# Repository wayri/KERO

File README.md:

# KERO — RC-programmed hello world pulse encoder

> **AI hardware-design experiment:** KERO evaluates AI-generated electronic schematics and PCB layouts. This is an experimental design for engineering review; hardware has not been built or bench tested.

One **CR2032** powers a repeating `hello world` pulse encoder made from **three TLV9044IPWR quad op-amps**, resistors and capacitors, with red/green LED indication. R/C values program the pulse sequence. The complete encoder, local libraries, 3D models, BoM and saved analysis are included on `main` following [PR #16](https://github.com/wayri/KERO/pull/16).

## Open the encoder

Open [encoder/Encoder.kicad_pro](encoder/Encoder.kicad_pro) in **KiCad 10** (saved verification: 10.0.6). The two-layer board is **40 × 40 mm**, with the circuit on the front and coin-cell holder on the back.

- [Encoder guide](encoder/README.md) · [BoM](encoder/bom.csv) · [Pin/net design intent](encoder/design-intent.json)
- [Schematic and shared variables](encoder/SCHEMATIC.md) · [Timing architecture and R/C values](encoded-model/architecture.md)
- [Front copper](encoder/previews/board-front.svg) · [Back copper](encoder/previews/board-back.svg)
- [Curved-routing evidence](encoder/evidence/curved-routing.json): native tangent arcs are the default; 678 staircase segments removed and 685 arc bends added.
- [Power, PI and thermal analysis files](encoder/analysis/README.md) — saved for the preceding straight-track board; copper overlays have not been rerun after smoothing.

All 79 fitted parts resolve local package models. The illustrated coin cell is a nominal envelope, not a manufacturer-qualified fit model. The CR2032 cell is a separate assembly item from BT1's holder; exact passive and LED order codes remain unverified in the BoM.

## Hierarchical schematic

The six wired sheets separate power, three timing banks and the output decoder. Shared project variables assign component values and common part details.

[Power](encoder/previews/Encoder-power.svg) · [Timing bank 1](encoder/previews/Encoder-bank1.svg) · [Timing bank 2](encoder/previews/Encoder-bank2.svg) · [Timing bank 3](encoder/previews/Encoder-bank3.svg) · [Output decoder](encoder/previews/Encoder-decoder.svg)

## Pulse sequence

Eleven inverting Schmitt op-amp stages form a timing ring. The twelfth channel combines the ring outputs through a resistive-majority network. Each complete frame emits the eleven symbols in `hello world`; the output and LEDs indicate the encoded pulses. The transmitter uses no MCU or separate logic IC.

| Pulse parameter | Programmed value |
|---|---|
| Codebook | space=0, d=1, e=2, h=3, l=4, o=5, r=6, w=7 |
| High pulse width | 50 ms × 1.3^code |
| Ordinary low gap | 100 ms |
| Final low gap / frame delimiter | 1 s |
| Nominal repeating frame | 3.664 s |
| Symbol-index payload | 33 bits, excluding codebook/framing overhead |

A receiver must recognize the long gap and decode the high pulse widths using this codebook. This is an electrical pulse output with LED indication, not ASCII, UART or radio. Changing R/C values changes the timing sequence. Startup, residual capacitor charge and supply ramps affect initial frames; see the [model boundaries and executed simulation](encoded-model/architecture.md) and [SPICE evidence](encoded-model/spice/README.md).

## Saved verification

| Check | Saved result |
|---|---|
| Schematic ERC | 0 violations across six sheets |
| PCB DRC / schematic parity | 0 reported findings / 0 mismatches |
| Connectivity | 0 open connections; all 40 nets connected |
| Circuit identity | 79 parts and 194 pad assignments checked |
| Routing repair | Dangling terminal stubs removed; track/via changes only |

[Board validation](encoder/evidence/board-validation.json) · [Native DRC](encoder/evidence/board-drc.json) · [Circuit equivalence](encoder/evidence/circuit-equivalence.json) · [Routing comparison](encoder/evidence/routing-change.json)

Five pre-existing default ignored DRC checks remain disclosed in the reports; no rule severity was relaxed. These are saved native checks and simulation evidence, not fabrication or bench qualification. Component sourcing, tolerances, leakage, startup and useful battery life still require hardware assessment.

## Coin-cell draw, losses and thermal analysis

These saved studies describe the preceding straight-track board revision. The circuit is unchanged, but PI and thermal copper overlays have not been rerun after smoothing.

| Saved model result | Value |
|---|---|
| Mean / RMS cell current at 3 V | 279.081 / 279.149 µA |
| Sampled settled peak current | 290.788 µA |
| Startup peak with 1 ms supply ramp | 1.174 mA |
| Component heat | 837.244 µW |
| Mean-load VBAT copper drop | 45.762 µV |
| Maximum board temperature at 25 °C ambient | 25.166 °C |

The [analysis index](encoder/analysis/README.md) includes native WayriCAD PI and QuickTherm results, extension-compatible companions, full compressed waveforms, per-component losses, cell-resistance scenarios, configurations, logs and source hashes.

These are model estimates. Local PI current-density peaks remain unconverged, and the mean-GND mesh has an unresolved region at C4. Ground fields use a shifted/reversed mathematical reference. QuickTherm estimates board temperature under declared material/convection assumptions; junction temperature, cell internal heat and electrothermal feedback are outside that solve. Vendor-model current reconstruction and other limitations remain documented. No measured battery-life claim is made.

## Review and comparison demos

[PR #16 — encoder, routing closure and analysis](https://github.com/wayri/KERO/pull/16) records the current project's development. [DEMO.md](DEMO.md) covers the comparison walkthrough, with earlier blinker changes in [PR #5](https://github.com/wayri/KERO/pull/5) (timing), [#6](https://github.com/wayri/KERO/pull/6) (layout), [#7](https://github.com/wayri/KERO/pull/7) (documentation), [#8](https://github.com/wayri/KERO/pull/8) (BoM), and [#9](https://github.com/wayri/KERO/pull/9) (mixed ECO).

## Legacy LED blinker

The root [KERO.kicad_pro](KERO.kicad_pro) is the earlier LMV358A alternating-LED oscillator, retained for historical comparisons. Its [schematic](previews/KERO.svg), [BoM](bom.csv) and [analysis](analysis/README.md) describe that older board. Use `encoder/Encoder.kicad_pro` and `encoder/analysis/` for the current pulse encoder.

## Models and attribution

Local KiCad library assets retain their [library license](LICENSE.KiCad.md), **CC-BY-SA-4.0 with the KiCad libraries exception**. See [asset provenance](ASSETS.md) and the [encoder model validation](encoder/evidence/board-validation.json). No IRCA files or proprietary thermal-camera circuitry are included.

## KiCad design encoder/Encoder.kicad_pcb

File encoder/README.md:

# KERO hello world encoder — draft hardware

> **AI hardware-design experiment:** KERO is an experiment to evaluate how well AI can generate and refine electronic schematics and PCB layouts. The designs are experimental candidates for engineering review and validation.

Saved [encoder cell-draw, PI and QuickTherm studies](analysis/README.md) describe the preceding straight-track board revision; the copper fields have not been rerun for the curved routing.

Open [Encoder.kicad_pro](Encoder.kicad_pro) in KiCad 10. The [six-sheet schematic](Encoder.kicad_sch) implements an RC-programmed `hello world` PWM sequence using three TLV9044IPWR quad op amps, one CR2032 cell, and alternating red/green indication. See [circuit operation and timing](../encoded-model/architecture.md), [executed SPICE evidence](../encoded-model/spice/README.md), and [schematic/variables guide](SCHEMATIC.md).

| Saved design check | Result |
|---|---|
| Native schematic ERC | 0 violations |
| Components / pad assignments | 79 / 194; exact intent and schematic parity |
| Board size | 40 × 40 mm; 44.9% less area than the original blinker |
| Placement | Front circuit, bottom coin-cell holder |
| Native routing status | **Complete: 0 open connections; all 40 nets connected** |
| Native DRC / schematic parity | 0 reported findings / 0 mismatches |
| Models | All 79 fitted parts resolve local standard package models; nominal cell is illustrative |

The default routing style is **native tangent circular arcs at bends**, with straight runs and fixed pad/via/branch landings. The [curved-routing receipt](evidence/curved-routing.json) records 678 redundant staircase segments removed and 685 native arc bends. One clearance-constrained GND path keeps its original corridor. [Routing guidance](AGENTS.md) defines the convention for future edits.

The routing repair removed dangling terminal stubs and negotiated alternate copper paths without moving components or changing the circuit or rules. [Revision comparison](evidence/routing-change.json) records only track/via changes; [circuit equivalence](evidence/circuit-equivalence.json) independently checks all 79 parts and 194 assignments against the simulated design. The native ERC, DRC, parity and connectivity checks pass. Five pre-existing default ignored DRC checks remain listed in the report; no severities or exclusions were changed.

This is a review candidate, not a fabrication release. [Board validation](evidence/board-validation.json) lists the connected pad partitions and check settings; [native DRC](evidence/board-drc.json) retains all reported findings. Source hashes were checked against the files being published. KiCad local preference files and tool scratch are excluded from Git; the original native command receipt retains the local preference-file hash as incidental execution context.

The [BoM](bom.csv) contains values, packages, manufacturer/MPN fields and ratings. Exact passive and LED order codes remain unverified and are marked `Select to specification`; no procurement closure is claimed. The CR2032 cell is a separate assembly consumable from BT1, the Keystone holder. Local KiCad libraries and package models follow the repository [asset provenance](../ASSETS.md) and [KiCad library license](../LICENSE.KiCad.md).

The root `KERO.kicad_*` files remain the earlier validated blinker. Saved PI/QuickTherm files under `../analysis/` describe that root board only; no new encoder PI or thermal solve is represented by those files.

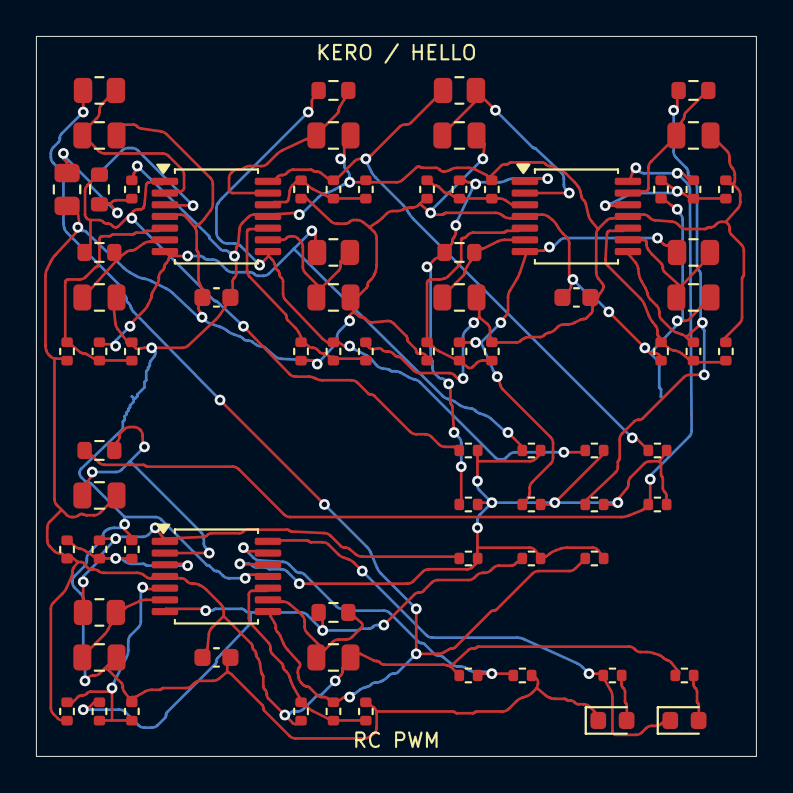
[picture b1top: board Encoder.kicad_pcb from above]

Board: 2 copper layers, 40.0 x 40.0 mm, 79 parts (1 on the bottom side), 40 nets.

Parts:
BT1: CR2032; BatteryHolder_Keystone_1058_1x2032
C1, C2, C3, C4, C5, C6, C7, C8, C9, C10, C11: 47n; C_0805_2012Metric
C12, C13, C14: 100n; C_0603_1608Metric
D1: RED; LED_0603_1608Metric
D2: GREEN; LED_0603_1608Metric
R1: 6.98M; R_0805_2012Metric
R2: 2.13M; R_0805_2012Metric
R3: 1.05M; R_0603_1608Metric
R4: 117k; R_0402_1005Metric
R5: 1.65M; R_0603_1608Metric
R6: 365k; R_0402_1005Metric
R7, R26: 208k; R_0402_1005Metric
R8: 412k; R_0402_1005Metric
R9: 3.52M; R_0805_2012Metric
R10: 182k; R_0402_1005Metric
R11: 332k; R_0402_1005Metric
R12: 665k; R_0402_1005Metric
R13: 1.47M; R_0603_1608Metric
R14: 427k; R_0402_1005Metric
R15: 213k; R_0402_1005Metric
R16: 340k; R_0402_1005Metric
R17, R37: 2.43M; R_0805_2012Metric
R18, R38: 240k; R_0402_1005Metric
R19, R39: 258k; R_0402_1005Metric
R20, R40: 511k; R_0402_1005Metric
R21, R29, R33: 2M; R_0603_1608Metric
R22, R27, R30, R34: 291k; R_0402_1005Metric
R23, R31, R35: 229k; R_0402_1005Metric
R24, R32, R36: 459k; R_0402_1005Metric
R25: 2.91M; R_0805_2012Metric
R28: 583k; R_0402_1005Metric
R41: 1.37M; R_0603_1608Metric
R42: 470k; R_0402_1005Metric
R43: 237k; R_0402_1005Metric
R44: 274k; R_0402_1005Metric
R45, R46, R47, R48, R49, R50, R51, R52, R53, R54, R55: 1M; R_0402_1005Metric
R56, R57: 100k; R_0402_1005Metric
R58, R59: 15k; R_0402_1005Metric
U1, U2, U3: TLV9044IPWR; TSSOP-14_4.4x5mm_P0.65mm

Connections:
/GND: BT1.2, C2.2, C4.2, C6.2, C8.2, C10.2, C12.2, C13.2, C14.2, D1.1, R4.2, R8.2, R12.2, R16.2, R20.2, R24.2, R28.2, R32.2, R36.2, R40.2, R44.2, R57.2, U1.11, U2.11, U3.11
/ST01_OUT: R3.2, R5.1, R45.1, U1.1
/ST02_OUT: R7.2, R9.1, R46.1, U1.7
/ST03_OUT: R11.2, R13.1, R47.1, U1.8
/ST04_OUT: R15.2, R17.1, R48.1, U1.14
/ST05_OUT: R19.2, R21.1, R49.1, U2.1
/ST06_OUT: R23.2, R25.1, R50.1, U2.7
/ST07_OUT: R27.2, R29.1, R51.1, U2.8
/ST08_OUT: R31.2, R33.1, R52.1, U2.14
/ST09_OUT: R35.2, R37.1, R53.1, U3.1
/ST10_OUT: R39.2, R41.1, R54.1, U3.7
/ST11_OUT: R1.1, R43.2, R55.1, U3.8
/VBAT: BT1.1, C1.2, C3.2, C5.2, C7.2, C9.2, C11.2, C12.1, C13.1, C14.1, R2.1, R6.1, R10.1, R14.1, R18.1, R22.1, R26.1, R30.1, R34.1, R38.1, R42.1, R56.1, R59.1, U1.4, U2.4, U3.4
/bank1/ST01_TH: R2.2, R3.1, R4.1, U1.3
/bank1/ST01_TIMING: C1.1, R1.2, U1.2
/bank1/ST02_TH: R6.2, R7.1, R8.1, U1.5
/bank1/ST02_TIMING: C2.1, R5.2, U1.6
/bank1/ST03_TH: R10.2, R11.1, R12.1, U1.10
/bank1/ST03_TIMING: C3.1, R9.2, U1.9
/bank1/ST04_TH: R14.2, R15.1, R16.1, U1.12
/bank1/ST04_TIMING: C4.1, R13.2, U1.13
/bank2/ST05_TH: R18.2, R19.1, R20.1, U2.3
/bank2/ST05_TIMING: C5.1, R17.2, U2.2
/bank2/ST06_TH: R22.2, R23.1, R24.1, U2.5
/bank2/ST06_TIMING: C6.1, R21.2, U2.6
/bank2/ST07_TH: R26.2, R27.1, R28.1, U2.10
/bank2/ST07_TIMING: C7.1, R25.2, U2.9
/bank2/ST08_TH: R30.2, R31.1, R32.1, U2.12
/bank2/ST08_TIMING: C8.1, R29.2, U2.13
/bank3/ST09_TH: R34.2, R35.1, R36.1, U3.3
/bank3/ST09_TIMING: C9.1, R33.2, U3.2
/bank3/ST10_TH: R38.2, R39.1, R40.1, U3.5
/bank3/ST10_TIMING: C10.1, R37.2, U3.6
/bank3/ST11_TH: R42.2, R43.1, R44.1, U3.10
/bank3/ST11_TIMING: C11.1, R41.2, U3.9
/decoder/GREEN_A: D2.2, R59.2
/decoder/MAJORITY_SUM: R45.2, R46.2, R47.2, R48.2, R49.2, R50.2, R51.2, R52.2, R53.2, R54.2, R55.2, U3.12
/decoder/MIDREF: R56.2, R57.1, U3.13
/decoder/RED_A: D1.2, R58.2
ENCODED_OUT: D2.1, R58.1, U3.14

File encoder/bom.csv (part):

Reference,Quantity,Value,Footprint,Manufacturer,MPN,Rating,Datasheet
U1,1,TLV9044IPWR,Encoder:TSSOP-14_4.4x5mm_P0.65mm,Texas Instruments,TLV9044IPWR,1.2–5.5 V RRIO quad op amp,https://www.ti.com/lit/ds/symlink/tlv9044.pdf
U2,1,TLV9044IPWR,Encoder:TSSOP-14_4.4x5mm_P0.65mm,Texas Instruments,TLV9044IPWR,1.2–5.5 V RRIO quad op amp,https://www.ti.com/lit/ds/symlink/tlv9044.pdf
U3,1,TLV9044IPWR,Encoder:TSSOP-14_4.4x5mm_P0.65mm,Texas Instruments,TLV9044IPWR,1.2–5.5 V RRIO quad op amp,https://www.ti.com/lit/ds/symlink/tlv9044.pdf
R1,1,6.98M,Encoder:R_0805_2012Metric,Select to specification,Select to specification,"0.1%, 0805; exact MPN unverified",
R2,1,2.13M,Encoder:R_0805_2012Metric,Select to specification,Select to specification,"0.1%, 0805; exact MPN unverified",
R3,1,1.05M,Encoder:R_0603_1608Metric,Select to specification,Select to specification,"0.1%, 0603; exact MPN unverified",
R4,1,117k,Encoder:R_0402_1005Metric,Select to specification,Select to specification,"0.1%, 0402; exact MPN unverified",
C1,1,47n,Encoder:C_0805_2012Metric,Select to specification,Select to specification,"47 nF, C0G, 1%, 0805; exact MPN unverified",
R5,1,1.65M,Encoder:R_0603_1608Metric,Select to specification,Select to specification,"0.1%, 0603; exact MPN unverified",
R6,1,365k,Encoder:R_0402_1005Metric,Select to specification,Select to specification,"0.1%, 0402; exact MPN unverified",
R7,1,208k,Encoder:R_0402_1005Metric,Select to specification,Select to specification,"0.1%, 0402; exact MPN unverified",
R8,1,412k,Encoder:R_0402_1005Metric,Select to specification,Select to specification,"0.1%, 0402; exact MPN unverified",
C2,1,47n,Encoder:C_0805_2012Metric,Select to specification,Select to specification,"47 nF, C0G, 1%, 0805; exact MPN unverified",
R9,1,3.52M,Encoder:R_0805_2012Metric,Select to specification,Select to specification,"0.1%, 0805; exact MPN unverified",
R10,1,182k,Encoder:R_0402_1005Metric,Select to specification,Select to specification,"0.1%, 0402; exact MPN unverified",
R11,1,332k,Encoder:R_0402_1005Metric,Select to specification,Select to specification,"0.1%, 0402; exact MPN unverified",
R12,1,665k,Encoder:R_0402_1005Metric,Select to specification,Select to specification,"0.1%, 0402; exact MPN unverified",
C3,1,47n,Encoder:C_0805_2012Metric,Select to specification,Select to specification,"47 nF, C0G, 1%, 0805; exact MPN unverified",
R13,1,1.47M,Encoder:R_0603_1608Metric,Select to specification,Select to specification,"0.1%, 0603; exact MPN unverified",
R14,1,427k,Encoder:R_0402_1005Metric,Select to specification,Select to specification,"0.1%, 0402; exact MPN unverified",
R15,1,213k,Encoder:R_0402_1005Metric,Select to specification,Select to specification,"0.1%, 0402; exact MPN unverified",
R16,1,340k,Encoder:R_0402_1005Metric,Select to specification,Select to specification,"0.1%, 0402; exact MPN unverified",
C4,1,47n,Encoder:C_0805_2012Metric,Select to specification,Select to specification,"47 nF, C0G, 1%, 0805; exact MPN unverified",
R17,1,2.43M,Encoder:R_0805_2012Metric,Select to specification,Select to specification,"0.1%, 0805; exact MPN unverified",
R18,1,240k,Encoder:R_0402_1005Metric,Select to specification,Select to specification,"0.1%, 0402; exact MPN unverified",
R19,1,258k,Encoder:R_0402_1005Metric,Select to specification,Select to specification,"0.1%, 0402; exact MPN unverified",
R20,1,511k,Encoder:R_0402_1005Metric,Select to specification,Select to specification,"0.1%, 0402; exact MPN unverified",
C5,1,47n,Encoder:C_0805_2012Metric,Select to specification,Select to specification,"47 nF, C0G, 1%, 0805; exact MPN unverified",
R21,1,2M,Encoder:R_0603_1608Metric,Select to specification,Select to specification,"0.1%, 0603; exact MPN unverified",
R22,1,291k,Encoder:R_0402_1005Metric,Select to specification,Select to specification,"0.1%, 0402; exact MPN unverified",
R23,1,229k,Encoder:R_0402_1005Metric,Select to specification,Select to specification,"0.1%, 0402; exact MPN unverified",
R24,1,459k,Encoder:R_0402_1005Metric,Select to specification,Select to specification,"0.1%, 0402; exact MPN unverified",
C6,1,47n,Encoder:C_0805_2012Metric,Select to specification,Select to specification,"47 nF, C0G, 1%, 0805; exact MPN unverified",
R25,1,2.91M,Encoder:R_0805_2012Metric,Select to specification,Select to specification,"0.1%, 0805; exact MPN unverified",
R26,1,208k,Encoder:R_0402_1005Metric,Select to specification,Select to specification,"0.1%, 0402; exact MPN unverified",
R27,1,291k,Encoder:R_0402_1005Metric,Select to specification,Select to specification,"0.1%, 0402; exact MPN unverified",
R28,1,583k,Encoder:R_0402_1005Metric,Select to specification,Select to specification,"0.1%, 0402; exact MPN unverified",
C7,1,47n,Encoder:C_0805_2012Metric,Select to specification,Select to specification,"47 nF, C0G, 1%, 0805; exact MPN unverified",
R29,1,2M,Encoder:R_0603_1608Metric,Select to specification,Select to specification,"0.1%, 0603; exact MPN unverified",
R30,1,291k,Encoder:R_0402_1005Metric,Select to specification,Select to specification,"0.1%, 0402; exact MPN unverified",
R31,1,229k,Encoder:R_0402_1005Metric,Select to specification,Select to specification,"0.1%, 0402; exact MPN unverified",
R32,1,459k,Encoder:R_0402_1005Metric,Select to specification,Select to specification,"0.1%, 0402; exact MPN unverified",
C8,1,47n,Encoder:C_0805_2012Metric,Select to specification,Select to specification,"47 nF, C0G, 1%, 0805; exact MPN unverified",
R33,1,2M,Encoder:R_0603_1608Metric,Select to specification,Select to specification,"0.1%, 0603; exact MPN unverified",
R34,1,291k,Encoder:R_0402_1005Metric,Select to specification,Select to specification,"0.1%, 0402; exact MPN unverified",
R35,1,229k,Encoder:R_0402_1005Metric,Select to specification,Select to specification,"0.1%, 0402; exact MPN unverified",
R36,1,459k,Encoder:R_0402_1005Metric,Select to specification,Select to specification,"0.1%, 0402; exact MPN unverified",
C9,1,47n,Encoder:C_0805_2012Metric,Select to specification,Select to specification,"47 nF, C0G, 1%, 0805; exact MPN unverified",
R37,1,2.43M,Encoder:R_0805_2012Metric,Select to specification,Select to specification,"0.1%, 0805; exact MPN unverified",
R38,1,240k,Encoder:R_0402_1005Metric,Select to specification,Select to specification,"0.1%, 0402; exact MPN unverified",
R39,1,258k,Encoder:R_0402_1005Metric,Select to specification,Select to specification,"0.1%, 0402; exact MPN unverified",
R40,1,511k,Encoder:R_0402_1005Metric,Select to specification,Select to specification,"0.1%, 0402; exact MPN unverified",
C10,1,47n,Encoder:C_0805_2012Metric,Select to specification,Select to specification,"47 nF, C0G, 1%, 0805; exact MPN unverified",
R41,1,1.37M,Encoder:R_0603_1608Metric,Select to specification,Select to specification,"0.1%, 0603; exact MPN unverified",
R42,1,470k,Encoder:R_0402_1005Metric,Select to specification,Select to specification,"0.1%, 0402; exact MPN unverified",
R43,1,237k,Encoder:R_0402_1005Metric,Select to specification,Select to specification,"0.1%, 0402; exact MPN unverified",
R44,1,274k,Encoder:R_0402_1005Metric,Select to specification,Select to specification,"0.1%, 0402; exact MPN unverified",
C11,1,47n,Encoder:C_0805_2012Metric,Select to specification,Select to specification,"47 nF, C0G, 1%, 0805; exact MPN unverified",
R45,1,1M,Encoder:R_0402_1005Metric,Select to specification,Select to specification,"0.1%, 0402; exact MPN unverified",
R46,1,1M,Encoder:R_0402_1005Metric,Select to specification,Select to specification,"0.1%, 0402; exact MPN unverified",
R47,1,1M,Encoder:R_0402_1005Metric,Select to specification,Select to specification,"0.1%, 0402; exact MPN unverified",
R48,1,1M,Encoder:R_0402_1005Metric,Select to specification,Select to specification,"0.1%, 0402; exact MPN unverified",
R49,1,1M,Encoder:R_0402_1005Metric,Select to specification,Select to specification,"0.1%, 0402; exact MPN unverified",
R50,1,1M,Encoder:R_0402_1005Metric,Select to specification,Select to specification,"0.1%, 0402; exact MPN unverified",
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
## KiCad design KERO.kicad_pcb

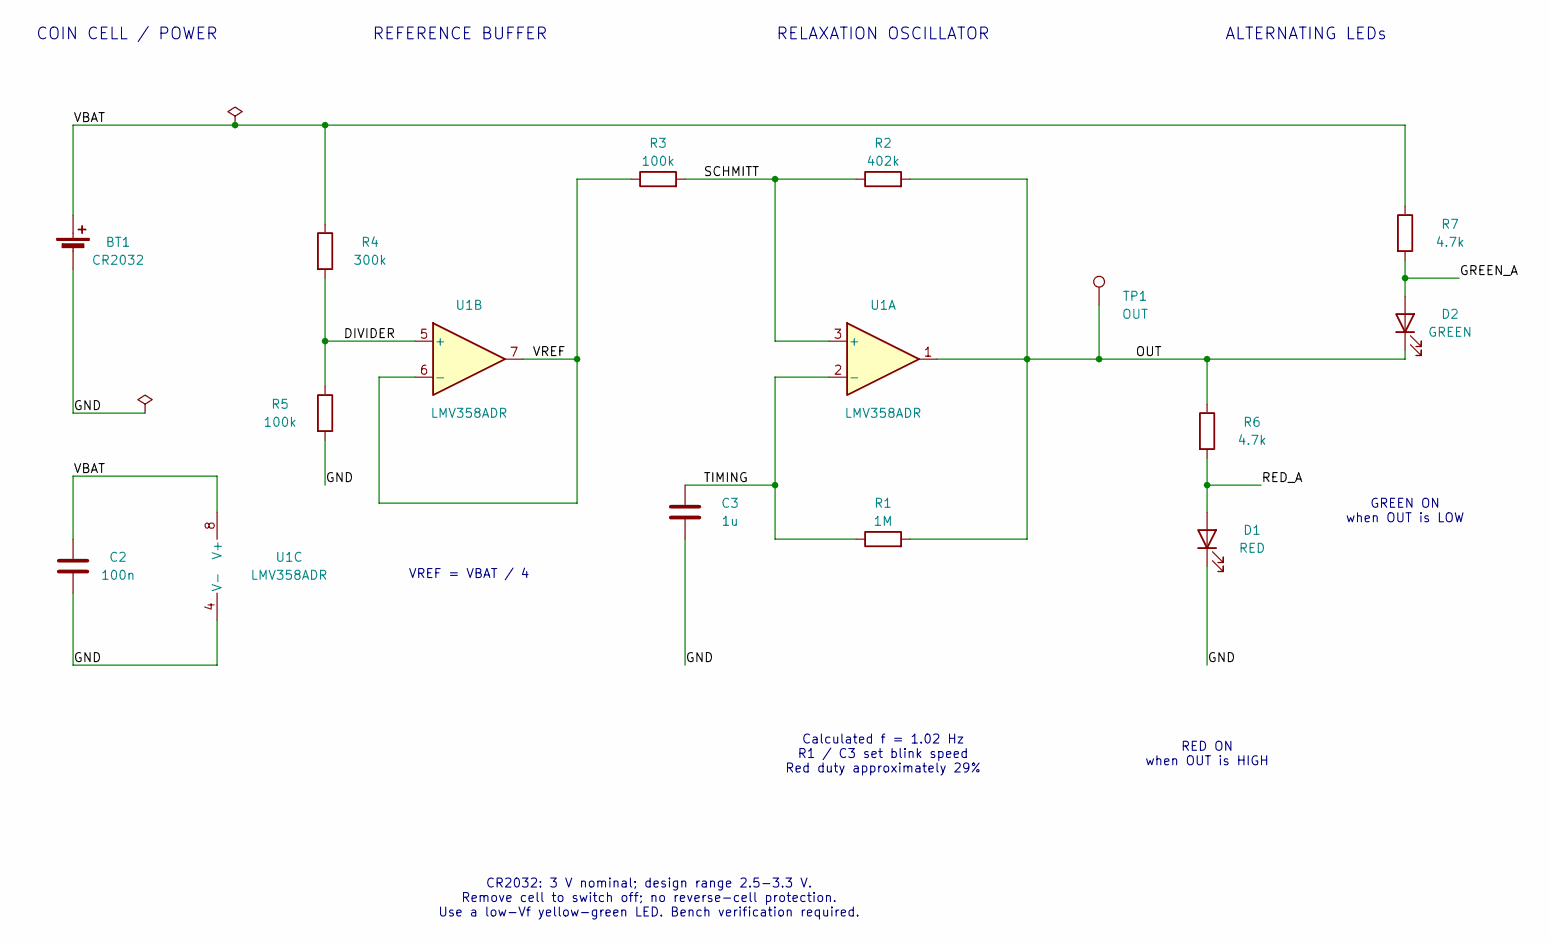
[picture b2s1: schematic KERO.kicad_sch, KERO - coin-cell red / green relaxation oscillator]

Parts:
BT1: CR2032; BatteryHolder_Keystone_1058_1x2032; Rating Keystone 1058 holder; one CR2032, 3 V n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; MPN 1058
C2: 100n; C_0603_1608Metric; Rating 10 V min, X7R, +/-10%, 0603; MPN Select to specification
C3: 1u; C_Rect_L7.2mm_W4.5mm_P5.00mm; Rating 1 uF, >=16 V, +/-10%, film, radial P5 m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; MPN Select to specification
D1: RED; LED_D5.0mm; Rating 5 mm diffused red LED; low-current type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; MPN Select to specification
D2: GREEN; LED_D5.0mm; Rating 5 mm diffused yellow-green LED; Vf <=2.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; MPN Select to specification
R1: 1M; R_0603_1608Metric; Rating 1%, 0.1 W, 0603; MPN Select to specification
R2: 402k; R_0603_1608Metric; Rating 1%, 0.1 W, 0603; MPN Select to specification
R3, R5: 100k; R_0603_1608Metric; Rating 1%, 0.1 W, 0603; MPN Select to specification
R4: 300k; R_0603_1608Metric; Rating 1%, 0.1 W, 0603; MPN Select to specification
R6, R7: 4.7k; R_0603_1608Metric; Rating 4.7 kohm, 1%, >=0.1 W, 0603, thick film; MPN CRCW06034K70FKEA
TP1: OUT; TestPoint_Loop_D2.50mm_Drill1.0mm; Rating 2.5 mm loop test point, 1.0 mm drill; O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; MPN Select to specification
U1: LMV358ADR; SOIC-8_3.9x4.9mm_P1.27mm; Rating TI LMV358ADR, SOIC-8; 2.5 to 5.5 V; MPN LMV358ADR

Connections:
/DIVIDER: R4.2, R5.1, U1.5 (+)
/GND: BT1.2 (-), C2.2, C3.2, D1.1 (K), R5.2, U1.4 (V-)
/GREEN_A: D2.2 (A), R7.2
/OUT: D2.1 (K), R1.2, R2.2, R6.1, TP1.1, U1.1
/RED_A: D1.2 (A), R6.2
/SCHMITT: R2.1, R3.2, U1.3 (+)
/TIMING: C3.1, R1.1, U1.2 (-)
/VBAT: BT1.1 (+), C2.1, R4.1, R7.1, U1.8 (V+)
/VREF: R3.1, U1.6 (-), U1.7

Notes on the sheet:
COIN CELL / POWER
REFERENCE BUFFER
RELAXATION OSCILLATOR
ALTERNATING LEDs
VREF = VBAT / 4
Calculated f = 1.02 Hz R1 / C3 set blink speed Red duty approximately 29%
RED ON when OUT is HIGH
GREEN ON when OUT is LOW
CR2032: 3 V nominal; design range 2.5-3.3 V. Remove cell to switch off; no reverse-cell protection. Use a low-Vf yellow-green LED. Bench verification required.

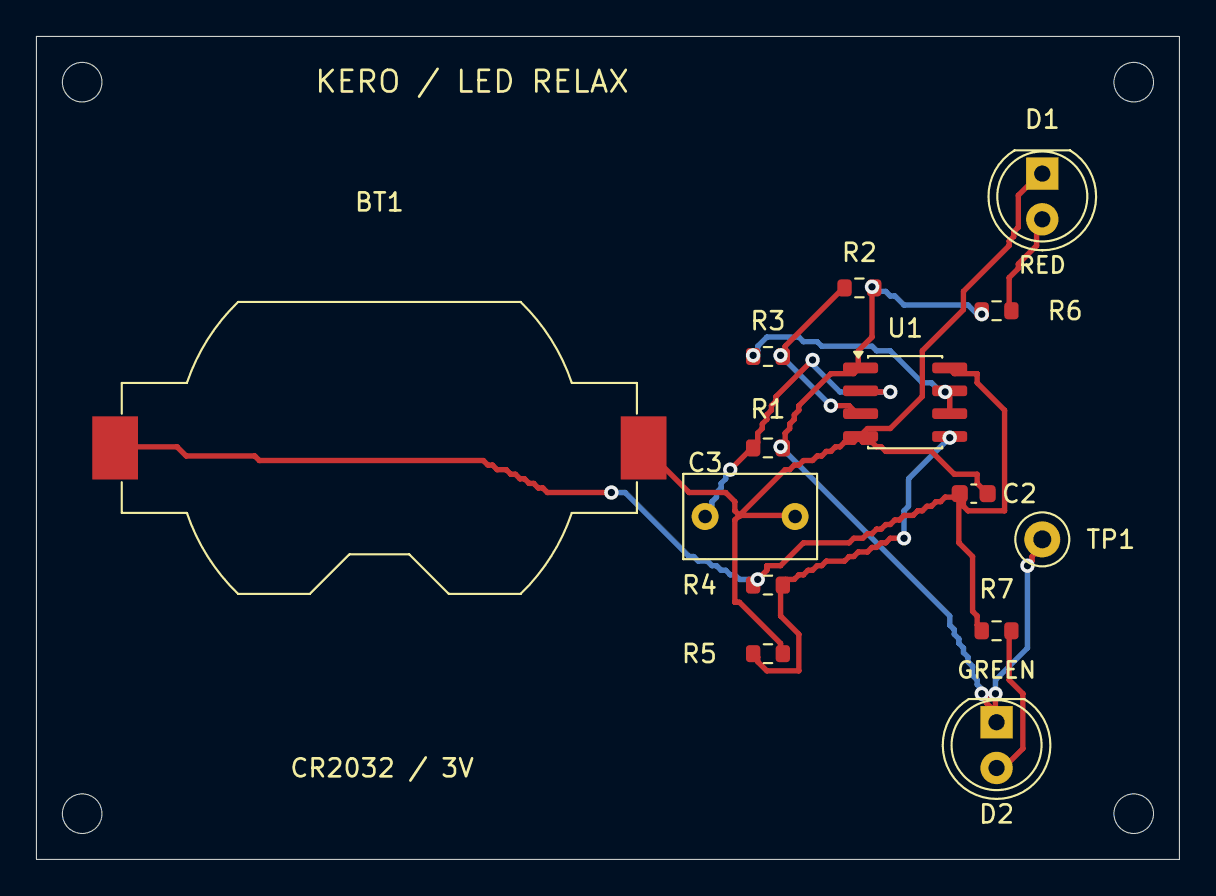
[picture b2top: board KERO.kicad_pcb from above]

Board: 2 copper layers, 63.5 x 45.7 mm, 18 parts (0 on the bottom side), 9 nets.

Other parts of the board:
H1, H2, H3, H4: MountingHole_2.2mm_M2

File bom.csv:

Reference,Quantity,Value,Footprint,Manufacturer,MPN,Rating,Datasheet
U1,1,LMV358ADR,Demo:SOIC-8_3.9x4.9mm_P1.27mm,Texas Instruments,LMV358ADR,"TI LMV358ADR, SOIC-8; 2.5 to 5.5 V",https://www.ti.com/lit/ds/symlink/lmv358a.pdf
R1,1,1M,Demo:R_0603_1608Metric,Generic,Select to specification,"1%, 0.1 W, 0603",
R2,1,402k,Demo:R_0603_1608Metric,Generic,Select to specification,"1%, 0.1 W, 0603",
R3,1,100k,Demo:R_0603_1608Metric,Generic,Select to specification,"1%, 0.1 W, 0603",
R4,1,300k,Demo:R_0603_1608Metric,Generic,Select to specification,"1%, 0.1 W, 0603",
R5,1,100k,Demo:R_0603_1608Metric,Generic,Select to specification,"1%, 0.1 W, 0603",
C2,1,100n,Demo:C_0603_1608Metric,Generic,Select to specification,"10 V min, X7R, +/-10%, 0603",
BT1,1,CR2032,Demo:BatteryHolder_Keystone_1058_1x2032,Keystone,1058,"Keystone 1058 holder; one CR2032, 3 V nominal",
R6,1,4.7k,Demo:R_0603_1608Metric,Vishay,CRCW06034K70FKEA,"4.7 kohm, 1%, >=0.1 W, 0603, thick film",https://www.vishay.com/docs/20035/dcrcwe3.pdf
D1,1,RED,Demo:LED_D5.0mm,Generic,Select to specification,"5 mm diffused red LED; low-current type, Vf <=2 V preferred",
R7,1,4.7k,Demo:R_0603_1608Metric,Vishay,CRCW06034K70FKEA,"4.7 kohm, 1%, >=0.1 W, 0603, thick film",https://www.vishay.com/docs/20035/dcrcwe3.pdf
D2,1,GREEN,Demo:LED_D5.0mm,Generic,Select to specification,5 mm diffused yellow-green LED; Vf <=2.1 V; avoid blue/InGaN green,
TP1,1,OUT,Demo:TestPoint_Loop_D2.50mm_Drill1.0mm,Generic,Select to specification,"2.5 mm loop test point, 1.0 mm drill; OUT probe access",
C3,1,1u,Demo:C_Rect_L7.2mm_W4.5mm_P5.00mm,Generic,Select to specification,"1 uF, >=16 V, +/-10%, film, radial P5 mm; verify body height",

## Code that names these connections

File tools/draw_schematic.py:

"""Readable native schematic presentation; electrical pin/net assignments stay unchanged."""
import copy,math
from build_demo import ROOT,Q,uid,sym,kids,one,dump,write
POSITIONS={'U1':(144.78,81.28,0),'R1':(144.78,106.68,90),'R2':(144.78,55.88,90),'R3':(113.03,55.88,90),'R4':(66.04,66.04,0),'R5':(66.04,88.9,0),'C1':(116.84,102.87,0),'C2':(30.48,110.49,0),'BT1':(30.48,66.04,0),'R6':(190.5,91.44,0),'D1':(190.5,106.68,90),'R7':(218.44,63.5,0),'D2':(218.44,76.2,90)}
def schematic(ps,variant):
 for p in ps:p['sch']=POSITIONS[p['ref']]
 libs={p['symbol']:sym(*p['symbol'].split(':')) for p in ps};libs['power:PWR_FLAG']=sym('power','PWR_FLAG')
 n=libs['Amplifier_Operational:LMV358']
 for k,v in [('Value','LMV358ADR'),('Datasheet','https://www.ti.com/lit/ds/symlink/lmv358a.pdf'),('Description','LMV358A dual low-voltage op amp; verified SOIC-8 pin map')]:next(x for x in kids(n,'property') if x[1]==k)[2]=Q(v)
 write(ROOT/'Demo.kicad_sym',dump(['kicad_symbol_lib',['version',20241209],['generator',Q('eeschema')]]+list(libs.values()))+'\n')
 cache=copy.deepcopy(list(libs.values()))
 for n in cache:n[1]=Q('Demo:'+n[1])
 sch=['kicad_sch',['version',20250114],['generator',Q('eeschema')],['uuid',Q(uid('root'))],['paper',Q('A4')],['title_block',['title',Q('KERO - coin-cell red / green relaxation oscillator')],['date',Q('2026-11-07')],['rev',Q(variant)]],['lib_symbols']+cache]
 def eff(size=1.27):return ['effects',['font',['size',size,size]]]
 def prop(k,v,x,y,angle=0,hidden=False):
  e=eff()
  if hidden:e.append(['hide','yes'])
  return ['property',Q(k),Q(v),['at',x,y,angle],e]
 def place(p,x,y,a=0,unit=1):
  ref=p['ref'];rx,ry,vx,vy=(x,y-7.62,x,y+7.62) if ref=='U1' else (x+6.35,y-1.27,x+6.35,y+1.27)
  if ref=='R5':rx,ry,vx,vy=x-6.35,y-1.27,x-6.35,y+1.27
  if ref=='U1' and unit==3:rx,ry,vx,vy=x+7.62,y-1.27,x+7.62,y+1.27
  if a==90 and ref.startswith('R'):rx,ry,vx,vy=x,y-5.08,x,y-2.54
  n=['symbol',['lib_id',Q('Demo:'+p['symbol'].replace(':','_'))],['at',x,y,a],['unit',unit],['in_bom','yes'],['on_board','yes'],['dnp','no'],['uuid',Q(uid(ref+('' if unit==1 else '-'+str(unit))))],prop('Reference',ref,rx,ry,90 if a==90 else 0),prop('Value',p['value'],vx,vy,90 if a==90 else 0),prop('Footprint','Demo:'+p['footprint'].split(':')[1] if p['footprint'].split(':')[1] else '',x,y,hidden=True),prop('Datasheet','https://www.ti.com/lit/ds/symlink/lmv358a.pdf' if ref=='U1' else '',x,y,hidden=True),prop('Manufacturer','Texas Instruments' if ref=='U1' else 'Keystone' if ref=='BT1' else 'Generic',x,y,hidden=True),prop('MPN','LMV358ADR' if ref=='U1' else '1058' if ref=='BT1' else 'Select to specification',x,y,hidden=True),prop('Rating',p['rating'],x,y,hidden=True),['instances',['project',Q('KERO'),['path',Q('/'+uid('root')),['reference',Q(ref)],['unit',unit]]]]]
  sch.append(n);return n
 for p in ps:place(p,*POSITIONS[p['ref']])
 u=next(p for p in ps if p['ref']=='U1');place(u,86.36,81.28,unit=2);place(u,53.34,110.49,unit=3)
 def path(*pts):
  for a,b in zip(pts,pts[1:]):
   assert a[0]==b[0] or a[1]==b[1],(a,b)
   sch.append(['wire',['pts',['xy',*a],['xy',*b]],['stroke',['width',0.2032],['type','default']],['uuid',Q(uid('wire'+str(a)+str(b)))]])
 def label(name,xy):
  e=eff();e.append(['justify','left','bottom'])
  sch.append(['label',Q(name),['at',*xy,0],e,['uuid',Q(uid('label'+name+str(xy)))]])
 def dot(xy):sch.append(['junction',['at',*xy],['diameter',0.9144],['color',0,0,0,0],['uuid',Q(uid('dot'+str(xy)))]])
 def note(key,s,x,y,size=1.27):sch.append(['text',Q(s),['at',x,y,0],eff(size),['uuid',Q(uid('drawing-note-'+key))]])
 # Visible supply bus: cell -> reference divider -> green LED branch.
 path((30.48,48.26),(53.34,48.26),(66.04,48.26),(218.44,48.26),(218.44,59.69));dot((53.34,48.26));dot((66.04,48.26));label('VBAT',(30.48,48.26))
 battery=next(p for p in ps if p['ref']=='BT1');pins={}
 for sub in kids(libs[battery['symbol']],'symbol'):
  for pin in kids(sub,'pin'):
   at=one(pin,'at');pins[one(pin,'number')[1]]=(30.48+float(at[1]),66.04-float(at[2]))
 path(pins['1'],(30.48,48.26));path(pins['2'],(30.48,88.9),(40.64,88.9));label('GND',(30.48,88.9))
 path((66.04,48.26),(66.04,62.23))
 # U1B reference buffer: a physically drawn divider and unity-gain feedback.
 path((66.04,69.85),(66.04,78.74),(66.04,85.09));dot((66.04,78.74));path((66.04,78.74),(78.74,78.74));label('DIVIDER',(68.58,78.74))
 path((66.04,92.71),(66.04,99.06));label('GND',(66.04,99.06))
 path((93.98,81.28),(101.6,81.28),(101.6,55.88),(109.22,55.88));dot((101.6,81.28));label('VREF',(95.25,81.28))
 path((101.6,81.28),(101.6,101.6),(73.66,101.6),(73.66,83.82),(78.74,83.82))
 # U1A Schmitt feedback: VREF -> R3 -> + input, OUT -> R2 -> + input.
 path((116.84,55.88),(129.54,55.88),(140.97,55.88));dot((129.54,55.88));label('SCHMITT',(119.38,55.88))
 path((129.54,55.88),(129.54,78.74),(137.16,78.74))
 path((148.59,55.88),(165.1,55.88),(165.1,81.28),(165.1,106.68),(148.59,106.68));dot((165.1,81.28))
 # Main output continues directly to both alternating LED current paths.
 path((152.4,81.28),(165.1,81.28),(190.5,81.28),(218.44,81.28));dot((190.5,81.28));label('OUT',(172.72,81.28))
 # RC relaxation path, with an unmistakable capacitor T junction.
 path((140.97,106.68),(129.54,106.68),(129.54,99.06),(129.54,83.82),(137.16,83.82));dot((129.54,99.06))
 path((116.84,99.06),(129.54,99.06));label('TIMING',(119.38,99.06))
 path((116.84,106.68),(116.84,124.46));label('GND',(116.84,124.46))
 # Red: OUT -> resistor -> LED -> GND. Green: VBAT -> resistor -> LED -> OUT.
 path((190.5,81.28),(190.5,87.63));path((190.5,95.25),(190.5,99.06),(190.5,102.87));dot((190.5,99.06));path((190.5,99.06),(198.12,99.06));label('RED_A',(198.12,99.06))
 path((190.5,110.49),(190.5,124.46));label('GND',(190.5,124.46))
 path((218.44,67.31),(218.44,69.85),(218.44,72.39));dot((218.44,69.85));path((218.44,69.85),(226.06,69.85));label('GREEN_A',(226.06,69.85))
 path((218.44,80.01),(218.44,81.28))
 # U1 power unit and its bypass capacitor form one wired group.
 path((30.48,106.68),(30.48,97.79),(50.8,97.79),(50.8,102.87));label('VBAT',(30.48,97.79))
 path((30.48,114.3),(30.48,124.46),(50.8,124.46),(50.8,118.11));label('GND',(30.48,124.46))
 for ref,xy in [('#FLG001',(53.34,48.26)),('#FLG002',(40.64,88.9))]:
  f={'ref':ref,'symbol':'power:PWR_FLAG','value':'PWR_FLAG','footprint':':','rating':''};n=place(f,*xy);one(n,'in_bom')[1]='no';one(n,'on_board')[1]='no'
  for propnode in kids(n,'property'):one(propnode,'effects').append(['hide','yes'])
 for key,title,x in [('power','COIN CELL / POWER',38.1),('ref','REFERENCE BUFFER',85.09),('osc','RELAXATION OSCILLATOR',144.78),('led','ALTERNATING LEDs',204.47)]:note(key,title,x,35.56,1.65)
 note('vref','VREF = VBAT / 4',86.36,111.76)
 rt=470000 if variant=='timing' else 1000000;lo=.25*402/502;hi=lo+100/502;t=rt*1e-6*(math.log((1-lo)/(1-hi))+math.log(hi/lo))
 note('timing',f'Calculated f = {1/t:.2f} Hz\nR1 / C1 set blink speed\nRed duty approximately 29%',144.78,137.16)
 note('red','RED ON\nwhen OUT is HIGH',190.5,137.16)
 note('green','GREEN ON\nwhen OUT is LOW',218.44,102.87)
 note('limits','CR2032: 3 V nominal; design range 2.5-3.3 V.\nRemove cell to switch off; no reverse-cell protection.\nUse a low-Vf yellow-green LED. Bench verification required.',111.76,157.48)
 write(ROOT/'KERO.kicad_sch',dump(sch)+'\n')

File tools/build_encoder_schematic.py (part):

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part('D2','Device:LED','GREEN','LED_SMD:LED_0603_1608Metric',{'1':'ENCODED_OUT','2':'GREEN_A'},'Low-Vf yellow-green; generic SPICE model, exact MPN unverified')
part('BT1','Device:Battery_Cell','CR2032','Battery:BatteryHolder_Keystone_1058_1x2032',{'1':'VBAT','2':'GND'},'One CR2032 coin cell, 3 V nominal; holder only')
for i in range(12,15):part(f'C{i}','Device:C','100n','Capacitor_SMD:C_0603_1608Metric',{'1':'VBAT','2':'GND'},'10 V, X7R, 0603; exact MPN unverified','BYPASS_C')
next(p for p in parts if p['ref']=='U3')['pins'].update({'12':'MAJORITY_SUM','13':'MIDREF','14':'ENCODED_OUT'})
def native_net(net):
 if net=='ENCODED_OUT':return net
 if net.endswith(('_TIMING','_TH')):
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  y=35.56+i*10.16;r=sh.place(f'R{45+i}',76.2,y,90);sh.label(s['output'],(35.56,y),'hierarchical_label');sh.wire((35.56,y),r['1']);sh.wire(r['2'],(101.6,y))
 sh.wire(*[(101.6,35.56+i*10.16) for i in range(11)])
 for i in range(1,10):sh.dot((101.6,35.56+i*10.16))
 u=sh.place('U3',154.94,76.2,unit=4);sh.wire((101.6,73.66),u['12']);sh.dot((101.6,73.66));sh.label('MAJORITY_SUM',(114.3,73.66))
 a=sh.place('R56',129.54,101.6);b=sh.place('R57',129.54,124.46)
 sh.wire(a['2'],(129.54,114.3),b['1']);sh.dot((129.54,114.3));sh.wire((129.54,114.3),(139.7,114.3),(139.7,78.74),u['13']);sh.label('MIDREF',(132.08,114.3))
 sh.wire(a['1'],(129.54,88.9));sh.label('VBAT',(129.54,88.9));sh.wire(b['2'],(129.54,139.7));sh.label('GND',(129.54,139.7))
 out=(185.42,76.2);sh.wire(u['14'],out,(215.9,76.2));sh.dot(out);sh.label('ENCODED_OUT',out,'global_label')
 r=sh.place('R58',185.42,96.52);d=sh.place('D1',185.42,116.84,90);sh.wire(out,r['1']);sh.wire(r['2'],d['2']);stub(sh,'GND',d['1']);sh.label('RED_A',(185.42,106.68))
 r=sh.place('R59',215.9,43.18);d=sh.place('D2',215.9,63.5,90);stub(sh,'VBAT',r['1']);sh.wire(r['2'],d['2']);sh.wire(d['1'],(215.9,76.2));sh.label('GREEN_A',(215.9,53.34))
 for i,net in enumerate(['VBAT','GND']):sh.label(net,(167.64+i*25.4,152.4),'hierarchical_label');sh.wire((167.64+i*25.4,152.4),(167.64+i*25.4,144.78));sh.label(net,(167.64+i*25.4,144.78))
 sh.note('RED = encoded output HIGH; GREEN = LOW.\n11 equal resistors sum the delay-ring states.\nU3D compares with VBAT/2. Custom PWM alphabet.\nElectrical/visible output; no radio.',101.6,172.72)
 sh.save();return sh,['VBAT','GND']+[s['output'] for s in SPEC['stages']]
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 for (sh,names),(x,y,w,h) in zip(blocks,[(20.32,48.26,55.88,30.48),(101.6,48.26,55.88,45.72),(190.5,48.26,55.88,45.72),(20.32,106.68,55.88,50.8),(119.38,106.68,104.14,50.8)]):
  n=['sheet',['at',x,y],['size',w,h],['stroke',['width',0],['type','default']],['fill',['color',0,0,0,0]],['uuid',Q(sh.id)],prop('Sheetname',sh.name,x,y-2.54),prop('Sheetfile',sh.name+'.kicad_sch',x,y+h+2.54)]
  for i,net in enumerate(names):
   yy=round(y+5.08+i*3.81,4);xx=x+w;n.append(['pin',Q(net),'bidirectional',['at',xx,yy,0],effects(1.016),['uuid',root.unique('sheetpin')]]);root.wire((xx,yy),(xx+7.62,yy));root.label(net,(xx+7.62,yy),'global_label' if net=='ENCODED_OUT' else 'label')
  n.append(['instances',['project',Q(PROJECT),['path',Q('/'+ROOTID),['page',Q(str(blocks.index((sh,names))+2))]]]])
  root.n.append(n)
  descriptions={'power':'CR2032 cell\nU1–U3 supplies / bypass','bank1':'ST01–ST04 / U1A–U1D','bank2':'ST05–ST08 / U2A–U2D','bank3':'ST09–ST11 / U3A–U3C','decoder':'11 × 1 MΩ weighted sum\nU3D majority comparator\nRED / GREEN indication'}
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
